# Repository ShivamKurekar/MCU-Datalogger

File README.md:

# 📟 MCU_Datalogger

A compact, efficient, and flexible microcontroller-based datalogger

### 🔧 Project Overview
This project implements a data logging system using a microcontroller, designed in KiCad.

1. 2-layer PCB for simplicity and cost-efficiency. (2Layer branch)
2. 4-layer PCB for better signal integrity and power routing. (main branch)

## 2 Layer PCB view

## 4 Layer PCB View

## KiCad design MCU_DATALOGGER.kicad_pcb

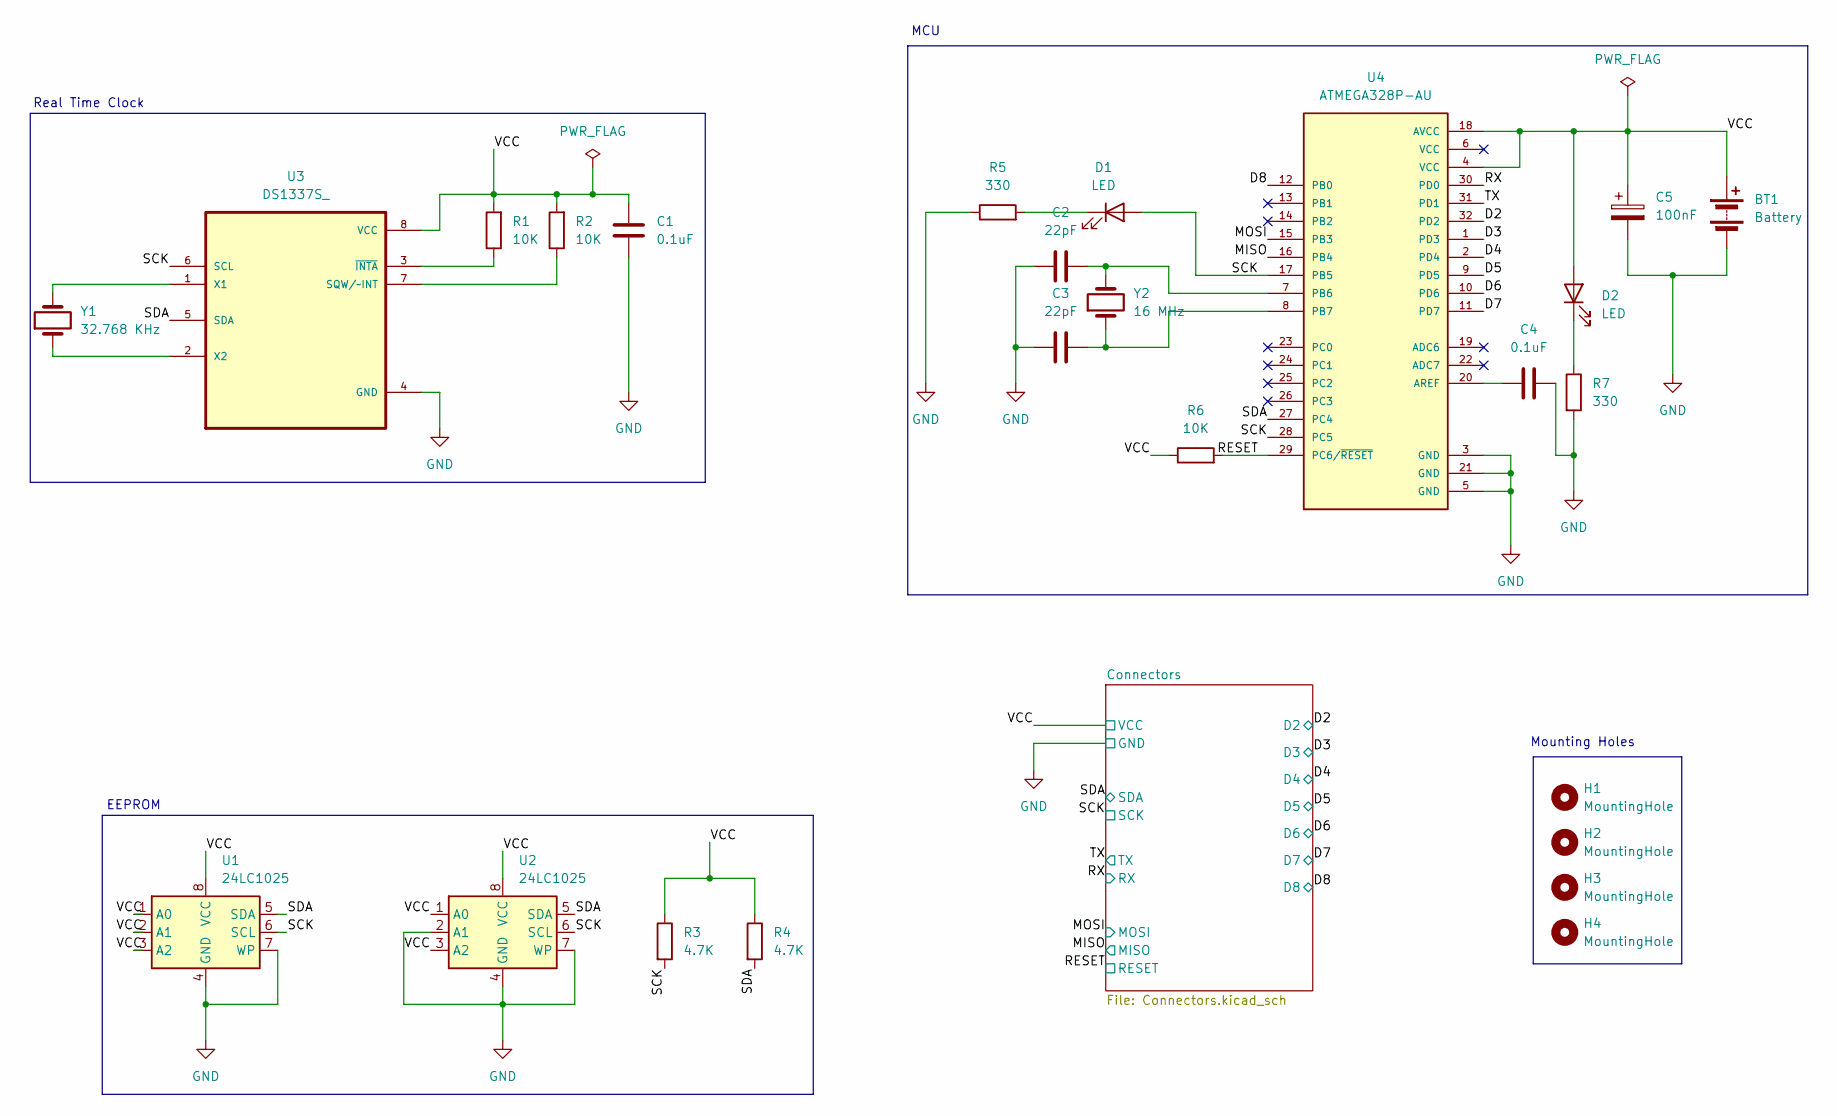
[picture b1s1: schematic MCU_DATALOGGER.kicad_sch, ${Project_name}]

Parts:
BT1: Battery; PinHeader_1x02_P2.54mm_Vertical
C1, C4: 0.1uF; C_0805_2012Metric
C2, C3: 22pF; C_0805_2012Metric
C5: 100nF; C_0805_2012Metric
D1, D2: LED; LED_0805_2012Metric
H1, H2, H3, H4: MountingHole; MountingHole_2.1mm
R1, R2, R6: 10K; R_0805_2012Metric
R3, R4: 4.7K; R_0805_2012Metric
R5, R7: 330; R_0805_2012Metric
U1, U2: 24LC1025; SOIC-8_5.3x5.3mm_P1.27mm
U3: DS1337S_; SOIC127P600X175-8N
U4: ATMEGA328P-AU; QFP80P900X900X120-32N; PARTREV 8271A
Y1: 32.768 KHz; Crystal_SMD_5032-2Pin_5.0x3.2mm_HandSoldering
Y2: 16 MHz; Crystal_SMD_5032-2Pin_5.0x3.2mm_HandSoldering

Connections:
/D2: U4.32 (PD2); also elsewhere on the board
/D3: U4.1 (PD3); also elsewhere on the board
/D4: U4.2 (PD4); also elsewhere on the board
/D5: U4.9 (PD5); also elsewhere on the board
/D6: U4.10 (PD6); also elsewhere on the board
/D7: U4.11 (PD7); also elsewhere on the board
/D8: U4.12 (PB0); also elsewhere on the board
/MISO: U4.16 (PB4); also elsewhere on the board
/MOSI: U4.15 (PB3); also elsewhere on the board
/RESET: R6.2, U4.29 (PC6/~RESET); also elsewhere on the board
/RX: U4.30 (PD0); also elsewhere on the board
/SCK: D1.2 (A), R3.2, U1.6 (SCL), U2.6 (SCL), U3.6 (SCL), U4.17 (PB5), U4.28 (PC5); also elsewhere on the board
/SDA: R4.2, U1.5 (SDA), U2.5 (SDA), U3.5 (SDA), U4.27 (PC4); also elsewhere on the board
/TX: U4.31 (PD1); also elsewhere on the board
/VCC: BT1.1 (+), C1.2, C5.1, D2.2 (A), R1.2, R2.2, R3.1, R4.1, R6.1, U1.1 (A0), U1.2 (A1), U1.3 (A2), U1.8 (VCC), U2.1 (A0), U2.3 (A2), U2.8 (VCC), U3.8 (VCC), U4.4 (VCC), U4.18 (AVCC); also elsewhere on the board
GND: BT1.2 (-), C1.1, C2.2, C3.1, C4.2, C5.2, R5.1, R7.2, U1.4 (GND), U1.7 (WP), U2.2 (A1), U2.4 (GND), U2.7 (WP), U3.4 (GND), U4.3 (GND), U4.5 (GND), U4.21 (GND); also elsewhere on the board
unnamed: D1.1 (K), R5.2
unnamed: D2.1 (K), R7.1
unnamed: R2.1, U3.7 (SQW/~INT)
unnamed: U3.1 (X1), Y1.2
unnamed: U3.2 (X2), Y1.1
unnamed: R1.1, U3.3 (~INTA)
unnamed: C4.1, U4.20 (AREF)
unnamed: C2.1, U4.7 (PB6), Y2.2
unnamed: C3.2, U4.8 (PB7), Y2.1

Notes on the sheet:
MCU
EEPROM
Mounting Holes
Real Time Clock

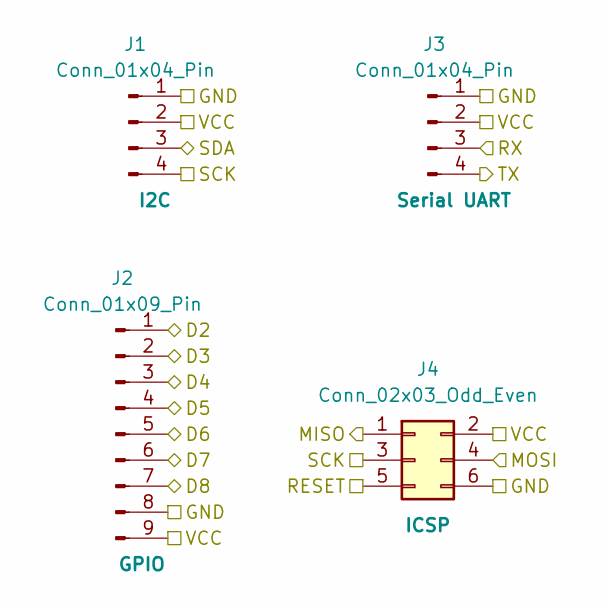
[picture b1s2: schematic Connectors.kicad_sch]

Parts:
J1, J3: Conn_01x04_Pin; PinHeader_1x04_P2.54mm_Vertical
J2: Conn_01x09_Pin; PinHeader_1x09_P2.54mm_Vertical
J4: Conn_02x03_Odd_Even; PinHeader_2x03_P2.54mm_Vertical

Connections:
/D2: J2.1; also elsewhere on the board
/D3: J2.2; also elsewhere on the board
/D4: J2.3; also elsewhere on the board
/D5: J2.4; also elsewhere on the board
/D6: J2.5; also elsewhere on the board
/D7: J2.6; also elsewhere on the board
/D8: J2.7; also elsewhere on the board
/MISO: J4.1; also elsewhere on the board
/MOSI: J4.4; also elsewhere on the board
/RESET: J4.5; also elsewhere on the board
/RX: J3.3; also elsewhere on the board
/SCK: J1.4, J4.3; also elsewhere on the board
/SDA: J1.3; also elsewhere on the board
/TX: J3.4; also elsewhere on the board
/VCC: J1.2, J2.9, J3.2, J4.2; also elsewhere on the board
GND: J1.1, J2.8, J3.1, J4.6; also elsewhere on the board

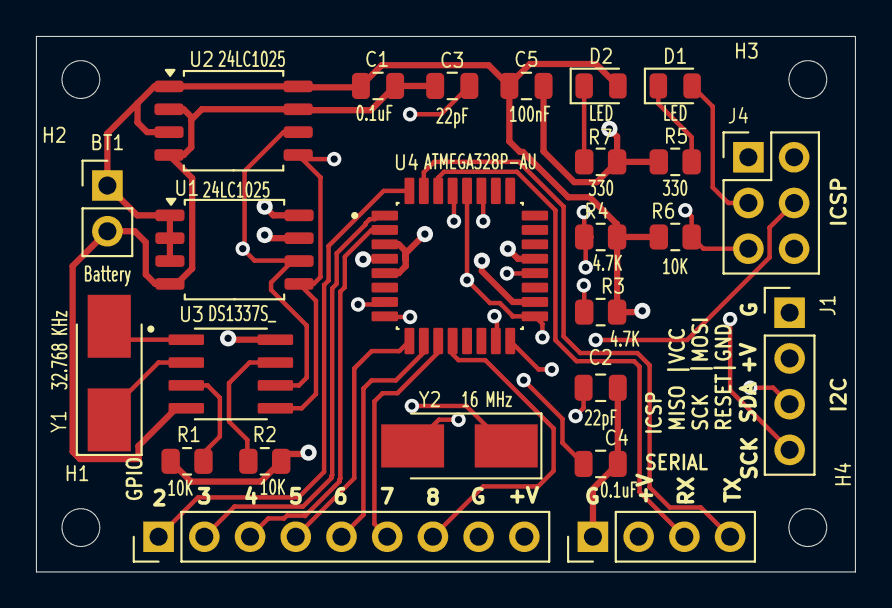
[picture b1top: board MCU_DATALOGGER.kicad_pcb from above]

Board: 4 copper layers, 45.5 x 29.8 mm, 29 parts (0 on the bottom side), 25 nets.

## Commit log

2025-05-22 Started making
2025-05-22 Added all symbols to the schematics
2025-05-22 Arranged symbols in schematics
2025-05-22 Associated all footprints to the symbols
2025-05-22 Wired all symbols in the schematics sheet 1
2025-05-22 Net classes is added
2025-05-22 Added comments to schematics
2025-05-22 Footprints added into layout
2025-05-22 Added & arranged footprints
2025-05-22 Footprints routed in layout
2025-05-22 Completed layout design of 2 layer
2025-05-22 Layout is completed and added 3D models too
2025-05-23 Fresh commit of all previous
2025-05-23 Completed routing of 4 layer PCB
2025-05-23 Added board characteristics of 4 layer PCB
